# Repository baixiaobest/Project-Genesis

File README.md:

# Project-Genesis
Genesis is a series of mini-size micro-controller designed and assembled by me.
It is general purpose micro-controller using Atmega 328 chip from Atmel company.
It is 100% compatible with Arduino Integrated Development Environment (IDE),
and as powerful as currently popular Arduino Uno but less in price and smaller in size.

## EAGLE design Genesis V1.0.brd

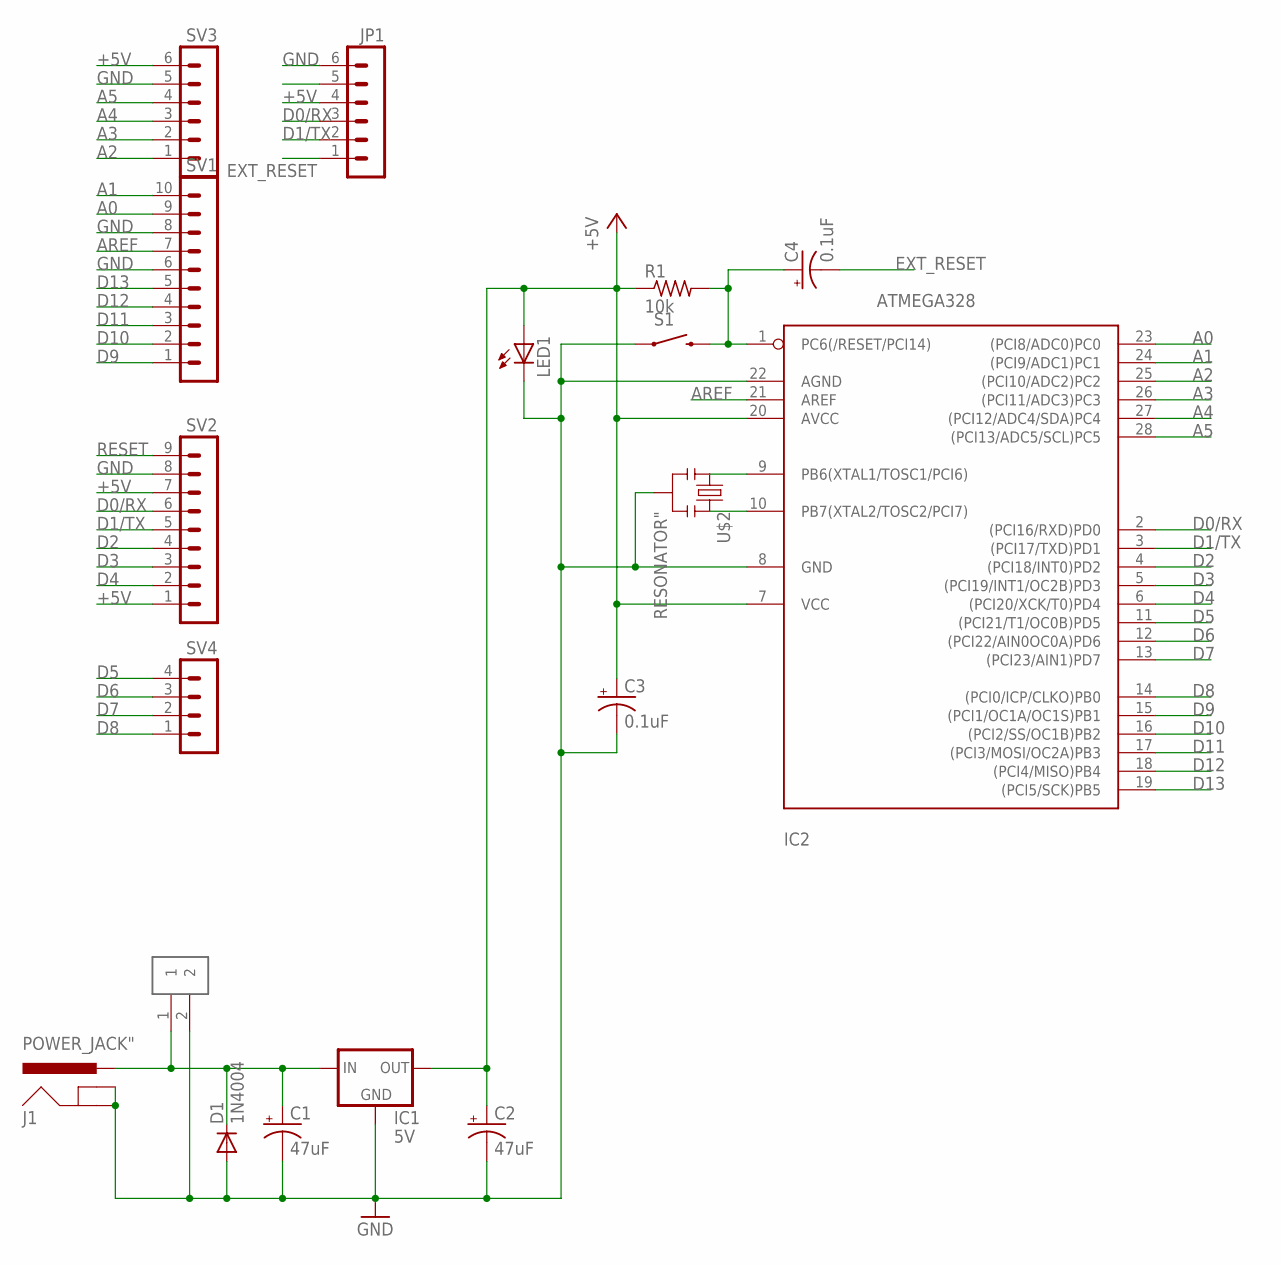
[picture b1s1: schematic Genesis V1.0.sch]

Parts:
C1, C2: 47uF; ELECTROLYTIC_CAP
C3, C4: 0.1uF; ELECTROLYTIC_CAP
D1: 1N4004; DO41-10
IC1: 5V; L4931_REGULATOR
IC2: ATMEGA328
J1: POWER_JACK"; POWER_JACK
JP1: MA06-1
LED1: LED3MM; LED
R1: 10k; RESISTOR
S1: MOMENTARY_SWITCH"; MOMENTARY_SWITCH
SV1: MA10-1
SV2: MA09-1
SV3: MA06-1
SV4: MA04-1
U$1: 1X02_HEADER
U$2: RESONATOR"; RESONATOR

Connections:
+5V: C2.+, C3.+, IC1.OUT, IC2.7 (VCC), IC2.20 (AVCC), JP1.4, LED1.A, R1.1, SV2.1, SV2.7, SV3.6
A0: IC2.23 ((PCI8/ADC0)PC0), SV1.9
A1: IC2.24 ((PCI9/ADC1)PC1), SV1.10
A2: IC2.25 ((PCI10/ADC2)PC2), SV3.1
A3: IC2.26 ((PCI11/ADC3)PC3), SV3.2
A4: IC2.27 ((PCI12/ADC4/SDA)PC4), SV3.3
A5: IC2.28 ((PCI13/ADC5/SCL)PC5), SV3.4
AREF: IC2.21 (AREF), SV1.7
D0/RX: IC2.2 ((PCI16/RXD)PD0), JP1.3, SV2.6
D1/TX: IC2.3 ((PCI17/TXD)PD1), JP1.2, SV2.5
D2: IC2.4 ((PCI18/INT0)PD2), SV2.4
D3: IC2.5 ((PCI19/INT1/OC2B)PD3), SV2.3
D4: IC2.6 ((PCI20/XCK/T0)PD4), SV2.2
D5: IC2.11 ((PCI21/T1/OC0B)PD5), SV4.4
D6: IC2.12 ((PCI22/AIN0OC0A)PD6), SV4.3
D7: IC2.13 ((PCI23/AIN1)PD7), SV4.2
D8: IC2.14 ((PCI0/ICP/CLKO)PB0), SV4.1
D9: IC2.15 ((PCI1/OC1A/OC1S)PB1), SV1.1
D10: IC2.16 ((PCI2/SS/OC1B)PB2), SV1.2
D11: IC2.17 ((PCI3/MOSI/OC2A)PB3), SV1.3
D12: IC2.18 ((PCI4/MISO)PB4), SV1.4
D13: IC2.19 ((PCI5/SCK)PB5), SV1.5
EXT_RESET: C4.-, JP1.1
GND: C1.-, C2.-, C3.-, D1.A, IC1.GND, IC2.8 (GND), IC2.22 (AGND), J1.GND, J1.GNDBREAK, JP1.6, LED1.K (C), S1.1, SV1.6, SV1.8, SV2.8, SV3.5, U$1.2, U$2.2
unnamed: C1.+, D1.C, IC1.IN, J1.PWR, U$1.1
unnamed: IC2.9 (PB6(XTAL1/TOSC1/PCI6)), U$2.1
unnamed: IC2.10 (PB7(XTAL2/TOSC2/PCI7)), U$2.3
RESET: C4.+, IC2.1 (PC6(/RESET/PCI14)), R1.2, S1.3 (2), SV2.9

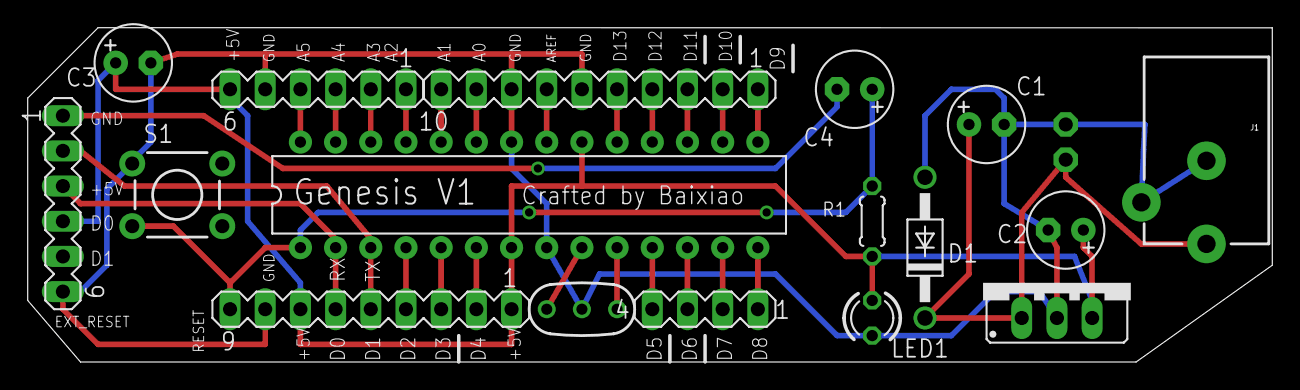
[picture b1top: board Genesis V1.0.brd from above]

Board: 2 copper layers, 89.8 x 24.1 mm, 18 parts (0 on the bottom side), 28 nets.

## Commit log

2015-02-10 genesis V1.0 pre-alpha
2016-05-21 clean up
